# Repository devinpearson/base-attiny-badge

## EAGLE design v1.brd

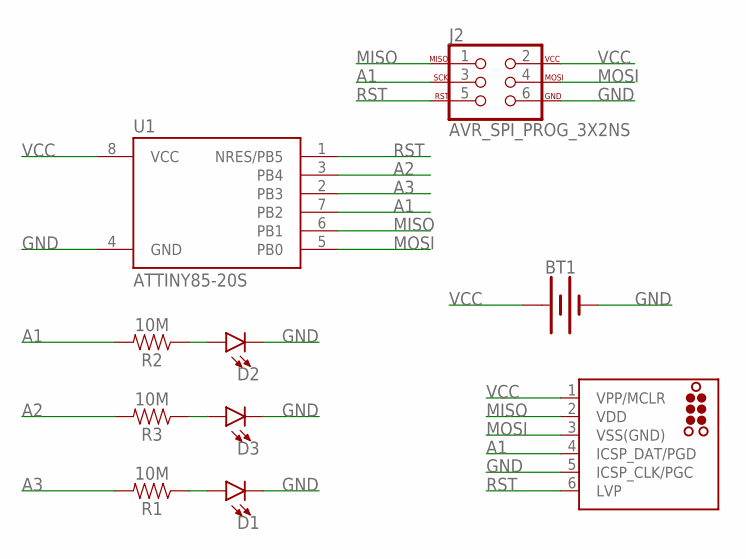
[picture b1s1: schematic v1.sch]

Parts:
BT1: BATTERY-20MM_SMD; BATTCON_20MM
D1, D2, D3: LED5MM; LED_5MM
J1: TC2030-MCP-NL
J2: AVR_SPI_PROG_3X2NS; 2X3-NS
R1, R2, R3: 10M; AXIAL-0.3
U1: ATTINY85-20S; SOIC8_EIAJ_208MIL

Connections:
A1: J1.4 (ICSP_DAT/PGD), J2.3, R2.P$2 (2), U1.7 (PB2)
A2: R3.P$2 (2), U1.3 (PB4)
A3: R1.P$2 (2), U1.2 (PB3)
GND: BT1.2 (-), D1.K (C), D2.K (C), D3.K (C), J1.5 (ICSP_CLK/PGC), J2.6, U1.4 (GND)
MISO: J1.2 (VDD), J2.1, U1.6 (PB1)
MOSI: J1.3 (VSS(GND)), J2.4, U1.5 (PB0)
unnamed: D1.A, R1.P$1 (1)
unnamed: D2.A, R2.P$1 (1)
unnamed: D3.A, R3.P$1 (1)
RST: J1.6 (LVP), J2.5, U1.1 (NRES/PB5)
VCC: BT1.1 (+), J1.1 (VPP/MCLR), J2.2, U1.8 (VCC)

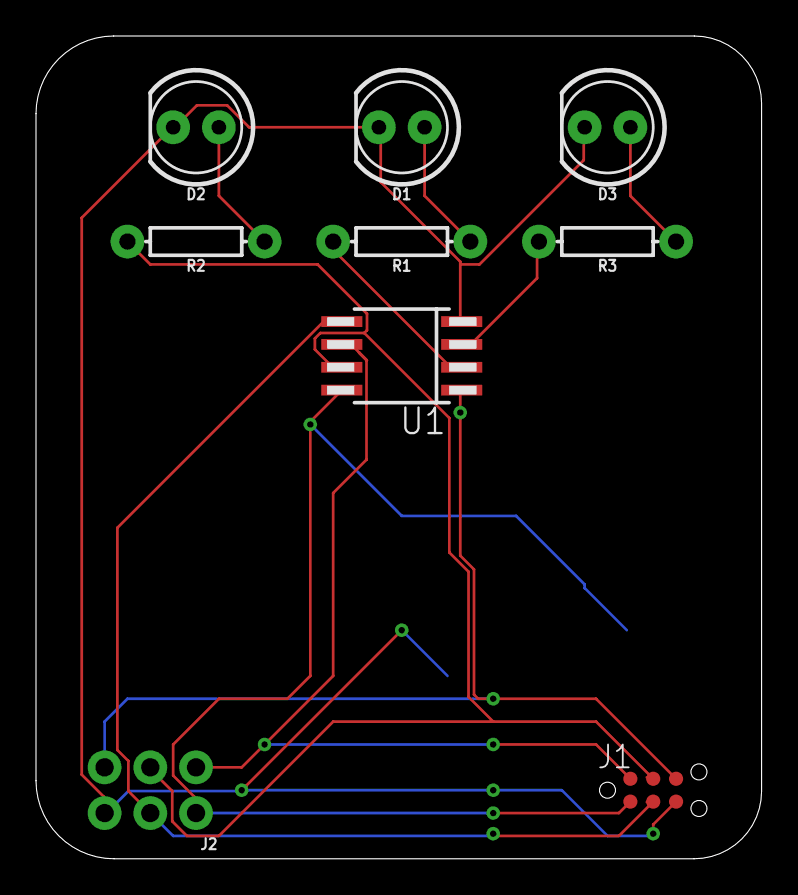
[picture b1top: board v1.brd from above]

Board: 2 copper layers, 40.3 x 45.7 mm, 10 parts (1 on the bottom side), 11 nets.

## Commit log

2020-01-07 initial files
2020-01-07 corrected floating via and improved position of via in bottom right as it was to close to the miso line
2020-01-09 moved battery to layer 2 and cleaned up tracks

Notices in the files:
parts and their libraries:
SparkFun-Batteries: Licensing: Creative Commons ShareAlike 4.0 International - https://creativecommons.org/licenses/by-sa/4.0
tag-connect: ©2009 ROFA.cz - modified and updated by Robert Darlington ‹rdarlington@gmail.com›
